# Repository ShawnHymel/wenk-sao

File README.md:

Wenk SAO
========
Wenk Shitty Add-On to be used as a training tool for the "Microcontrollers the Hard Way" workshop. See Documentation/Worksheet and Documentation/Slides for more information.

Solder connector on bottom to use as a Shitty Add-On for badges. Refer to [Shitty Add-On v1.69bis Standard](https://hackaday.io/project/52950-shitty-add-ons/log/159806-introducing-the-shitty-add-on-v169bis-standard) for more information.

VCC: 3.3-5 V
ATtiny84A@1MHz

Repository Contents
-------------------
* **Documentation** - Slides, worksheet, datasheets
* **Firmware** - Demo programs for the workshop
* **Hardware** - KiCad PCB files, BOM, Gerbers
* **Images** - Photos, diagrams, silkscreen artwork

License
-------
The hardware is released under [Creative Commons Attribution 4.0 International (CC BY 4.0)](https://creativecommons.org/licenses/by/4.0/).

The workshop slides and worksheet are released under [Creative Commons Attribution 4.0 International (CC BY 4.0)](https://creativecommons.org/licenses/by/4.0/).

Demo code in the Firmware directory is [Beerware](https://en.wikipedia.org/wiki/Beerware).

Distributed as-is; no warranty is given.

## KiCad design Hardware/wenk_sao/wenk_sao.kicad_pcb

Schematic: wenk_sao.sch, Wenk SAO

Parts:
C1: 10uF; C_0603_1608Metric; Digi-Key_PN 1276-1119-1-ND
C2: 0.1uF; C_0603_1608Metric; Digi-Key_PN 1276-1000-1-ND
D1, D2: LED_RABG; XZMDKCBDDG45S-9; Digi-Key_PN 1497-1257-1-ND
J1: Conn_01x06; Harwin_M20-89006xx_1x06_P2.54mm_Horizontal; Digi-Key_PN 952-3235-ND
JP1: SolderJumper_3_Bridged123; SolderJumper-3_P1.3mm_Bridged123_RoundedPad1.0x1.5mm
R1: 10k; R_0603_1608Metric; Digi-Key_PN 311-10.0KHRCT-ND
R2, R3: 4.7k; R_0603_1608Metric; Digi-Key_PN 311-4.70KHRCT-ND
R4, R7: 150; R_0603_1608Metric; Digi-Key_PN 311-150HRCT-ND
R5, R6, R8, R9: 100; R_0603_1608Metric; Digi-Key_PN 311-100HRCT-ND
U1: ATtiny84A-SSU; SOIC-14_3.9x8.7mm_P1.27mm; Digi-Key_PN ATTINY84A-SSURCT-ND
X1: Badgelife_sao_connector_v169bis; Badgelife-SAOv169-SAO-2x3_nopin1; Digi-Key_PN 732-5394-ND

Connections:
GND: C1.2, C2.2, J1.6, U1.14 (GND), X1.2
LED_A_BLUE: R5.2, U1.3 (XTAL2/PB1)
LED_A_GREEN: R6.2, U1.2 (XTAL1/PB0)
LED_A_RED: R4.2, U1.5 (PB2)
LED_B_BLUE: R8.2, U1.10 (PA3)
LED_B_GREEN: R9.2, U1.11 (PA2)
LED_B_RED: R7.2, U1.6 (PA7)
MISO: J1.1, U1.8 (PA5)
MOSI_SDA: J1.4, R2.2, U1.7 (PA6), X1.3
unnamed: D1.1, R4.1
unnamed: D1.3, R5.1
unnamed: D1.4, R6.1
unnamed: D2.1, R7.1
unnamed: D2.3, R8.1
unnamed: D2.4, R9.1
unnamed: JP1.1 (A), R2.1
unnamed: JP1.3 (B), R3.1
RST: J1.5, R1.2, U1.4 (~RESET~/PB3)
SCK_SCL: J1.3, R3.2, U1.9 (PA4), X1.4
VCC: C1.1, C2.1, D1.2, D2.2, J1.2, JP1.2 (C), R1.1, U1.1 (VCC), X1.1

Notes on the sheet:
AVR-ISP

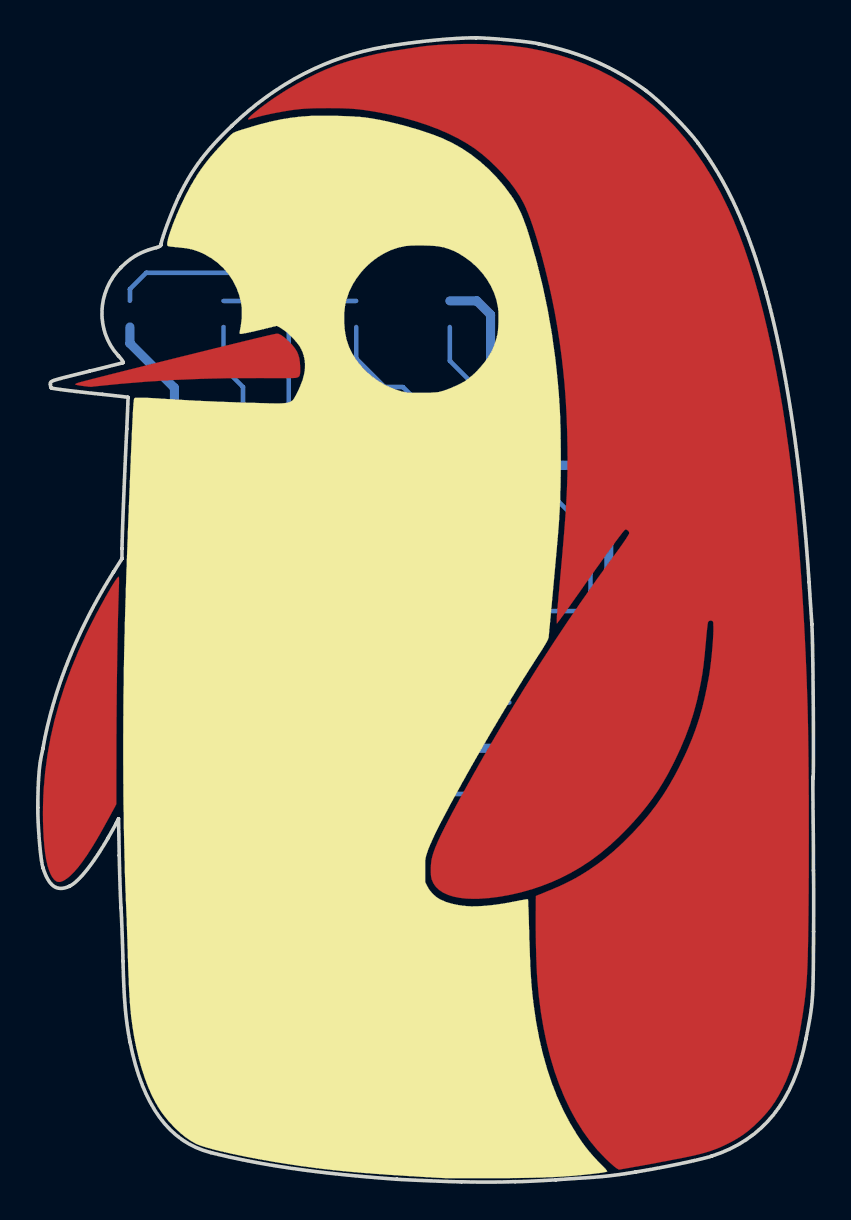
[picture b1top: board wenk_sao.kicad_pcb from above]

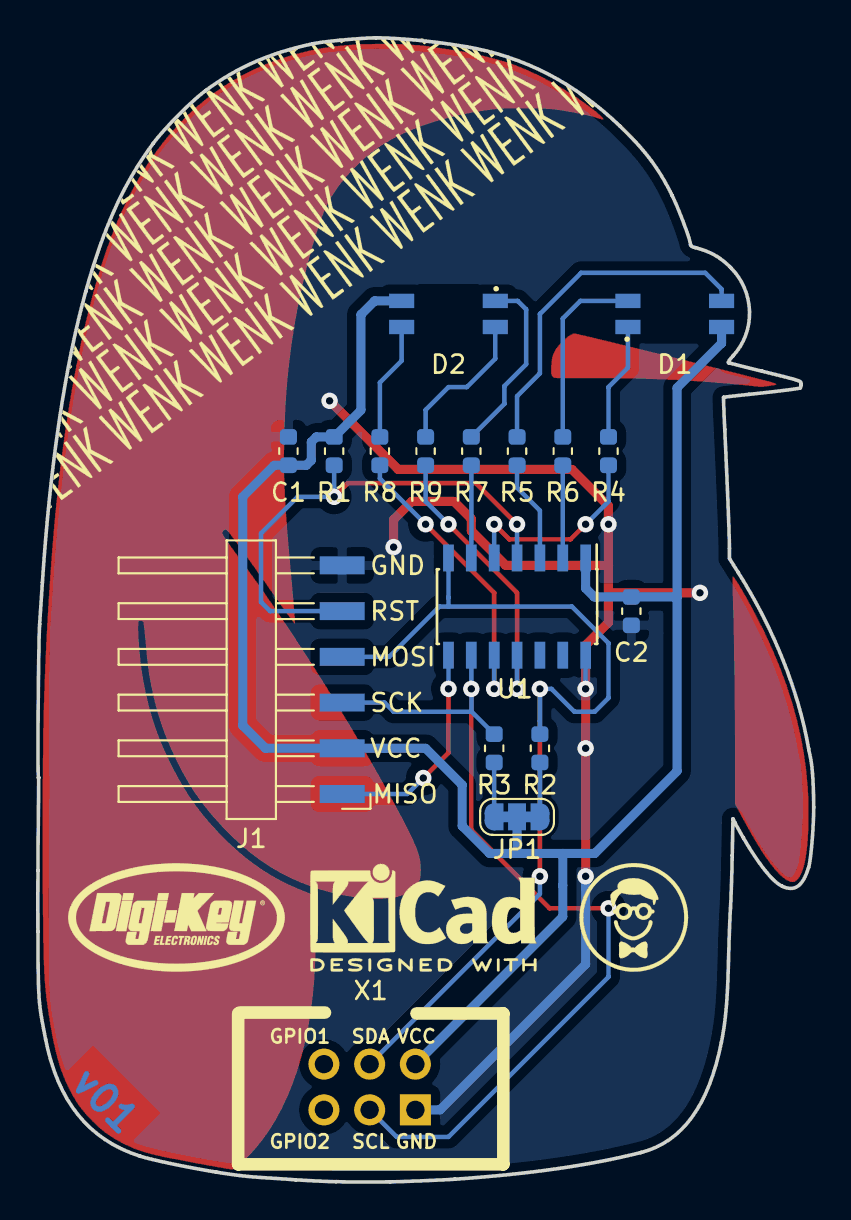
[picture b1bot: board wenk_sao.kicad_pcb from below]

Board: 2 copper layers, 43.1 x 63.6 mm, 17 parts (16 on the bottom side), 20 nets.

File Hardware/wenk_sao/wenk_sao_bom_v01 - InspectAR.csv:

Component,Description,Part,RefDes,Value,Footprint,Quantity Per PCB,Datasheet,MPN
1,Unpolarized capacitor,C,C2,0.1uF,C_0603_1608Metric,1,~,1276-1000-1-ND
2,Unpolarized capacitor,C,C1,10uF,C_0603_1608Metric,1,~,1276-1119-1-ND
3,"RGB LED, anode/red/green/blue",LED_RABG,D1 D2,LED_RABG,XZMDKCBDDG45S-9,2,~,1497-1257-1-ND
4,"Generic connector, single row, 01x06, script generated (kicad-library-utils/schlib/autogen/connector/)",Conn_01x06,J1,Conn_01x06,Harwin_M20-89006xx_1x06_P2.54mm_Horizontal,1,~,952-3235-ND
5,Resistor,R,R5 R6 R8 R9,100,R_0603_1608Metric,4,~,311-100HRCT-ND
6,Resistor,R,R1,10k,R_0603_1608Metric,1,~,311-10.0KHRCT-ND
7,Resistor,R,R4 R7,150,R_0603_1608Metric,2,~,311-150HRCT-ND
8,Resistor,R,R2 R3,4.7k,R_0603_1608Metric,2,~,311-4.70KHRCT-ND
9,"20MHz, 8kB Flash, 512B SRAM, 512B EEPROM, debugWIRE, SOIC-14",ATtiny84A-SSU,U1,ATtiny84A-SSU,SOIC-14_3.9x8.7mm_P1.27mm,1,http://ww1.microchip.com/downloads/en/DeviceDoc/doc8183.pdf,ATTINY84A-SSURCT-ND
10,,Badgelife_sao_connector_v169bis,X1,Badgelife_sao_connector_v169bis,Badgelife-SAOv169-SAO-2x3_nopin1,1,,732-5394-ND
,,,,,,,,
,,,,,,,,
,,,,,,,,
,,,,,,,,
,,,,,,,,
,,,,,,,,
,,,,,,,,
,,,,,,,,
,,,,,,,,
,,,,,,,,
,,,,,,,,
,,,,,,,,
,,,,,,,,
,,,,,,,,

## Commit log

2019-10-02 Schematic done. Part placement done. Test board outline import done.
2019-10-03 Gunter art layers done!
2019-10-04 v01 PCB layout complete
2019-10-08 Added silk labels to ISP header
2019-10-31 Added production test firmware
2019-10-31 Added ex 1 draft
2019-11-01 Added exercises and python uploader script
2019-11-02 Added software PWM example and rainbow example
2019-11-02 Added images
2019-11-02 Added slides and worksheet
2019-11-02 Renamed slides and worksheet
2019-11-12 Updated worksheet
2019-11-12 Created readme
2019-11-12 Added workshop license info
2019-11-27 Fixed slides

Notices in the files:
Hardware/wenk_sao/wenk_sao.kicad_pcb:
License: CC BY 4.0
